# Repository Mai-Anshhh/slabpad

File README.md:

# slabpad
My own macropad for gaming and video editing, It'll have 16 keys(4by4) and one rotary encoder for volume.

# Specifications
 
<ul>
<li>16x Cherry MX Switches <br>
<li>1x XIAO RP2040 <br>
<li>16x Blank DSA Keycaps <br>
<li>4x M3x16 Bolt <br>
<li>4x M3 Heatset <br>
<li>1x EC11 Rotary Encoder</li>  
</ul>

Others:
<ul>
<li>KMK Firmware
<li>hackpad (Assembly).f3z
</ul>

<h3>Schematic-</h3>

<h3>PCB</h3>

<h3>Case</h3>

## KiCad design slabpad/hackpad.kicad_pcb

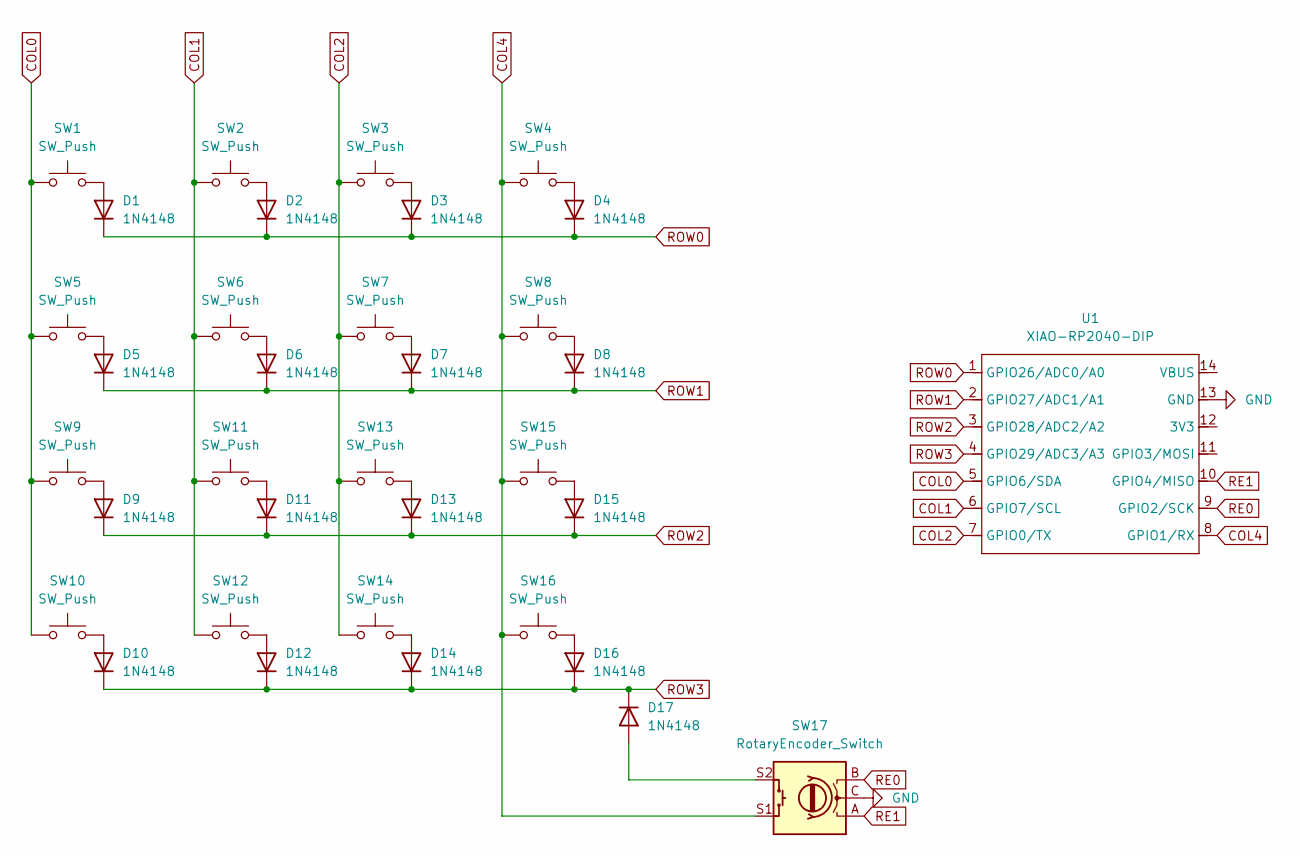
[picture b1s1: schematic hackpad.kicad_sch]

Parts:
D1, D2, D3, D4, D5, D6, D7, D8, D9, D10, D11, D12, D13, D14, D15, D16, D17: 1N4148; D_DO-35_SOD27_P7.62mm_Horizontal
SW1, SW2, SW3, SW4, SW5, SW6, SW7, SW8, SW9, SW10, SW11, SW12, SW13, SW14, SW15, SW16: SW_Push; SW_Cherry_MX_1.00u_PCB
SW17: RotaryEncoder_Switch; RotaryEncoder_Alps_EC11E-Switch_Vertical_H20mm
U1: XIAO-RP2040-DIP

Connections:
COL0: SW1.1, SW5.1, SW9.1, SW10.1, U1.5 (GPIO6/SDA)
COL1: SW2.1, SW6.1, SW11.1, SW12.1, U1.6 (GPIO7/SCL)
COL2: SW3.1, SW7.1, SW13.1, SW14.1, U1.7 (GPIO0/TX)
COL4: SW4.1, SW8.1, SW15.1, SW16.1, SW17.S1, U1.8 (GPIO1/RX)
GND: SW17.C, U1.13 (GND)
unnamed: D1.2 (A), SW1.2
unnamed: D2.2 (A), SW2.2
unnamed: D3.2 (A), SW3.2
unnamed: D4.2 (A), SW4.2
unnamed: D5.2 (A), SW5.2
unnamed: D6.2 (A), SW6.2
unnamed: D7.2 (A), SW7.2
unnamed: D8.2 (A), SW8.2
unnamed: D9.2 (A), SW9.2
unnamed: D10.2 (A), SW10.2
unnamed: D11.2 (A), SW11.2
unnamed: D12.2 (A), SW12.2
unnamed: D13.2 (A), SW13.2
unnamed: D14.2 (A), SW14.2
unnamed: D15.2 (A), SW15.2
unnamed: D16.2 (A), SW16.2
unnamed: D17.2 (A), SW17.S2
RE0: SW17.B, U1.9 (GPIO2/SCK)
RE1: SW17.A, U1.10 (GPIO4/MISO)
ROW0: D1.1 (K), D2.1 (K), D3.1 (K), D4.1 (K), U1.1 (GPIO26/ADC0/A0)
ROW1: D5.1 (K), D6.1 (K), D7.1 (K), D8.1 (K), U1.2 (GPIO27/ADC1/A1)
ROW2: D9.1 (K), D11.1 (K), D13.1 (K), D15.1 (K), U1.3 (GPIO28/ADC2/A2)
ROW3: D10.1 (K), D12.1 (K), D14.1 (K), D16.1 (K), D17.1 (K), U1.4 (GPIO29/ADC3/A3)

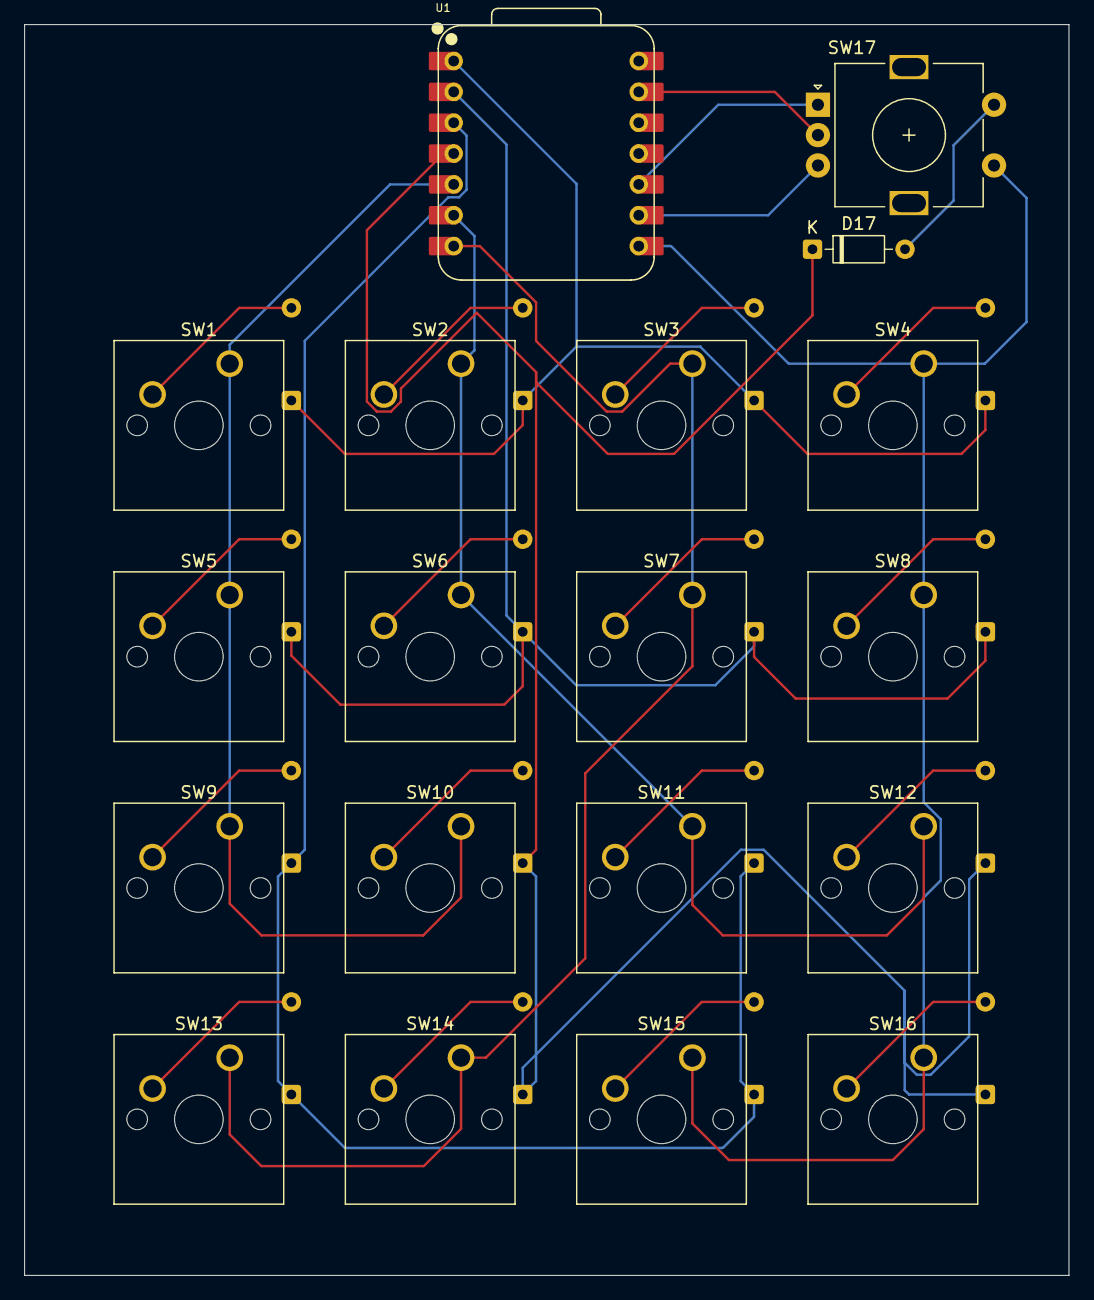
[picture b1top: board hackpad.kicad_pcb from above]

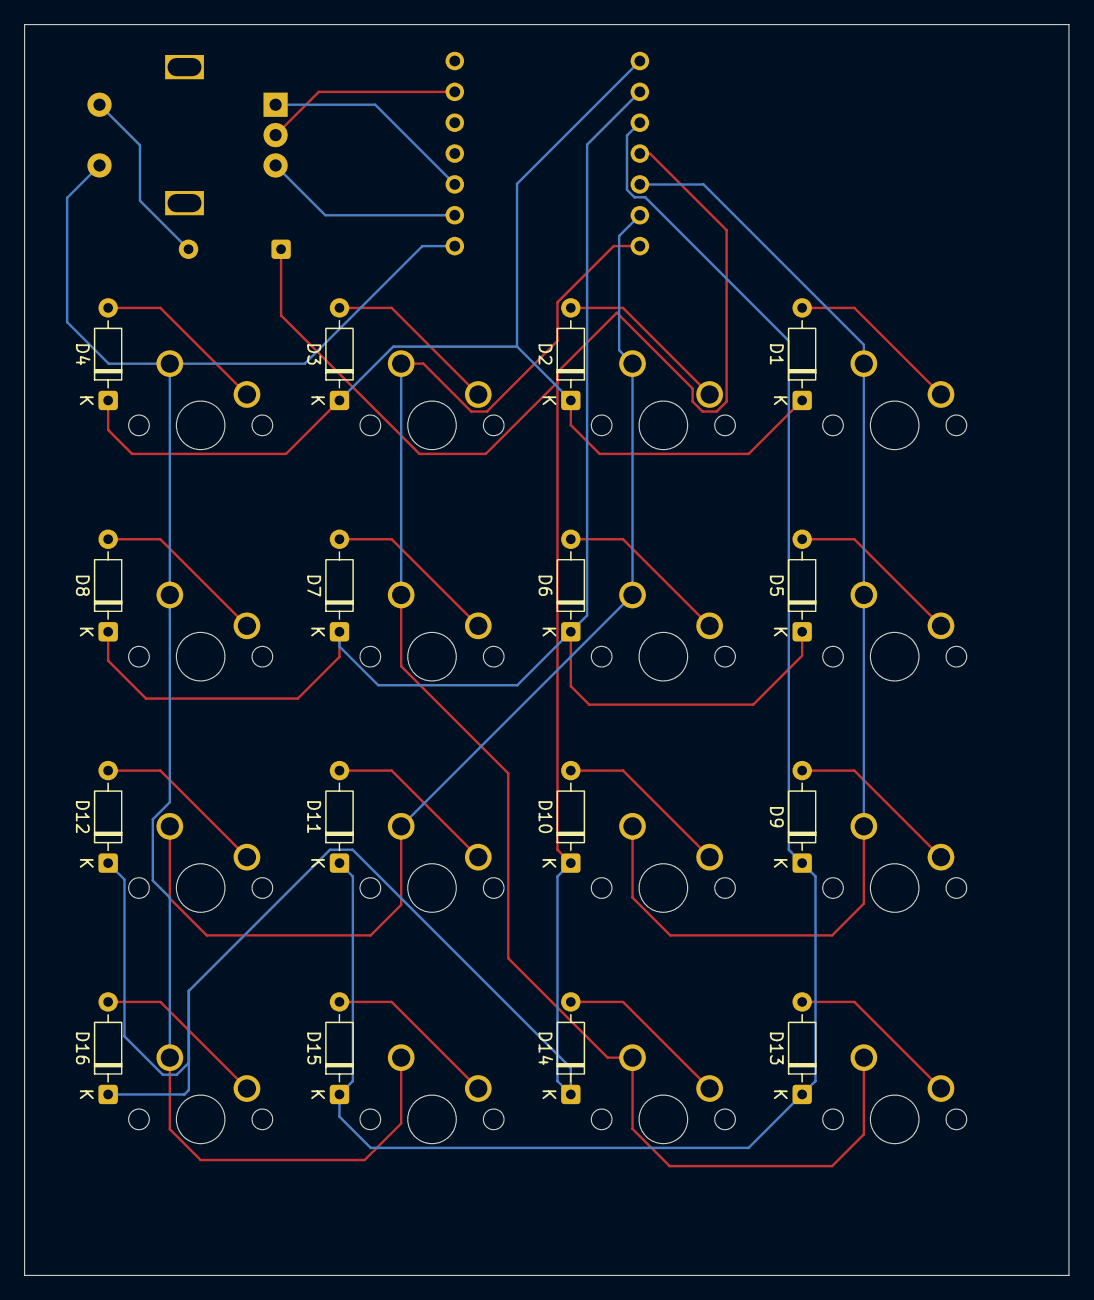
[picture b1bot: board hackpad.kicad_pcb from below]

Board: 2 copper layers, 86.0 x 103.0 mm, 35 parts (16 on the bottom side), 28 nets.

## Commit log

2026-03-28 Update README with project specifications and images
    Added specifications and images for the macropad project.
2026-03-28 Update quantity of Blank DSA Keycaps in README
2026-03-28 Update BOM for Slabpad with new quantities and totals
